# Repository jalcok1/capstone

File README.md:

capstone
========
This repo contains project related documents for the "Marionette DAQ"<br>

- [Visit the Wiki](https://github.com/jalcok1/capstone/wiki)

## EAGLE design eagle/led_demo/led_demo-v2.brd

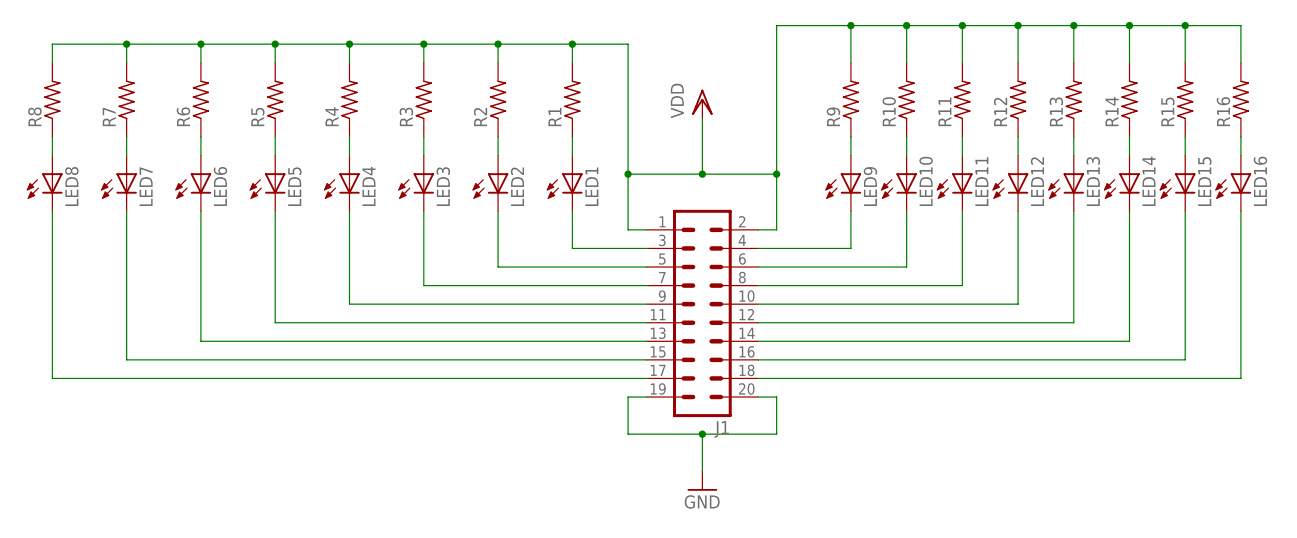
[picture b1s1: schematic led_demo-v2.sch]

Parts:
J1: MA10-2
LED1, LED2, LED3, LED4, LED5, LED6, LED7, LED8, LED9, LED10, LED11, LED12, LED13, LED14, LED15, LED16: LED3MM
R1, R2, R3, R4, R5, R6, R7, R8, R9, R10, R11, R12, R13, R14, R15, R16: R-US_0204/2V; 0204V

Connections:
GND: J1.19, J1.20
unnamed: LED8.A, R8.1
unnamed: LED7.A, R7.1
unnamed: LED6.A, R6.1
unnamed: LED5.A, R5.1
unnamed: LED4.A, R4.1
unnamed: LED3.A, R3.1
unnamed: LED2.A, R2.1
unnamed: LED1.A, R1.1
unnamed: J1.3, LED1.K (C)
unnamed: J1.5, LED2.K (C)
unnamed: J1.7, LED3.K (C)
unnamed: J1.9, LED4.K (C)
unnamed: J1.11, LED5.K (C)
unnamed: J1.13, LED6.K (C)
unnamed: J1.15, LED7.K (C)
unnamed: J1.17, LED8.K (C)
unnamed: J1.4, LED9.K (C)
unnamed: J1.6, LED10.K (C)
unnamed: J1.8, LED11.K (C)
unnamed: J1.10, LED12.K (C)
unnamed: J1.12, LED13.K (C)
unnamed: J1.14, LED14.K (C)
unnamed: J1.16, LED15.K (C)
unnamed: J1.18, LED16.K (C)
unnamed: LED16.A, R16.1
unnamed: LED15.A, R15.1
unnamed: LED14.A, R14.1
unnamed: LED13.A, R13.1
unnamed: LED12.A, R12.1
unnamed: LED11.A, R11.1
unnamed: LED10.A, R10.1
unnamed: LED9.A, R9.1
VDD: J1.1, J1.2, R1.2, R2.2, R3.2, R4.2, R5.2, R6.2, R7.2, R8.2, R9.2, R10.2, R11.2, R12.2, R13.2, R14.2, R15.2, R16.2

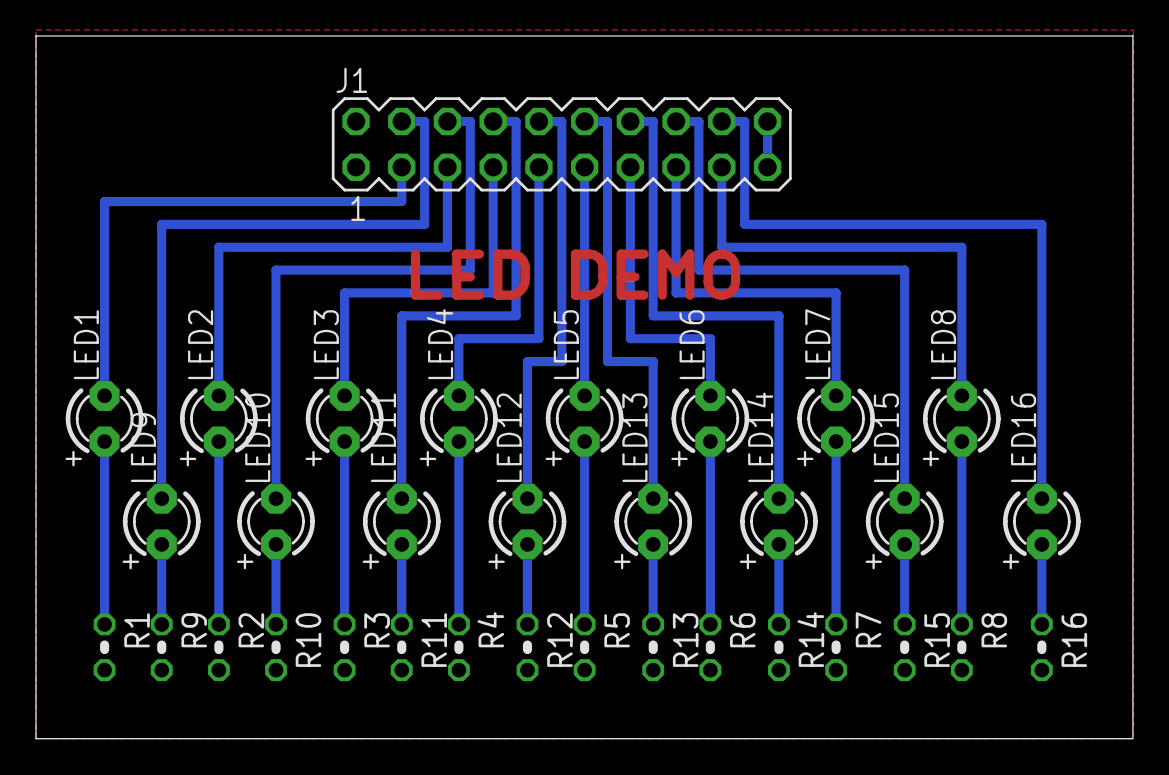
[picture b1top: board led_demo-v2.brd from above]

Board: 2 copper layers, 60.9 x 39.0 mm, 33 parts (0 on the bottom side), 34 nets.

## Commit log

2014-12-17 Daq List
2014-12-17 Empty Commit Message
2014-12-17 Starting research .xls document for seth and I to use :-)
2014-12-17 Update README.md
    Adding DAQ websites
2014-12-17 Opposition DAQs
2014-12-18 Added one research item and aditional formatting changes
2014-12-18 Added updates from capstone research xls to Research.xls
2014-12-18 Added USB-201 and USB-202 entries to the Research.xls spreadsheet
2014-12-29 Message can't be blank
2014-12-29 creating second research document so seth and I can do research using the same formatt without running into merge conflicts
2014-12-29 Adding new counter and counter resolution columns to Research2.xls spreadsheet
2014-12-29 small changes
2015-01-05 Updated Spreadsheet
2015-01-05 Added Digitial I/O column to Research2.xls and input more data
2015-01-06 More small changes
2015-01-07 DAQ's now show whether they have GPIO or not
2015-01-07 Seth Update
2015-01-09 Added matrix of STM32 MCU's, this list will be used for MCU selection in Marionette
2015-01-09 Added project info to README.md
2015-01-10 Added aditional formatting and highlighted some of the most likely candidates for marionette usage
2015-01-10 Level0 Marionette block diagram table
2015-01-11 Adding first draft of marionette level 0 block diagram
2015-01-11 Repo cleanup. Removed redundant research file.
2015-01-12 Finished rough draft of marionette level 0 block diagram
2015-01-12 finished marionette level 1 block diagram rough draft. level 1 table still needs updating
2015-01-13 Added Level 2 block diagram of the power management system
2015-01-13 Level 2 block diagram
    Updated the Level 2 block diagram to be more uniform and added it to the
    Functional Diagram document.
2015-01-13 Minor Editing to level2 block diagram; changed module name and description in the table
2015-01-13 editing changes
2015-01-13 repo clean up
2015-01-13 more repo cleanup
2015-01-13 repo cleanup.
2015-01-13 Update README.md
    Adding link to the capstone Wiki
2015-01-13 Added some changes, to function diagram
2015-01-14 Week 2 meeting notes 1/13/2015
    All corrections and weekly assignments from weekly meetings will be set up as issues.
2015-01-15 Added Level 0 block diagram changes as per request from week2 meeting
2015-01-15 Remved daq_list.rtf, this document contained redundant information that is also in daq_research.xls
2015-01-15 Level 1 and Level 2 block diagram revisions
    Edited both block diagrams as per our previous discussions. Waiting team
    review review before closing out issue
2015-01-15 Added a decision matrix on page2 of STM32matrix.xlsx
2015-01-17 Created folder for data sheets and added the STM3207i data sheet for reference
2015-01-17 Finished level0 and level1 block diagram changes
2015-01-17 Added Reference, programming, and user manuals
2015-01-18 first pass of marionette pin assignment
2015-01-20 2nd draft functional diagram
2015-01-21 Updated Marionette connections spreadsheet
    Added columns for ETH, SDIO, DAC2, and SYS. Added worksheet reserved for
    the 35 pins used for VDD, VREF, etc.
2015-01-21 formatting changes
2015-01-21 Added reserved pins to pin function sheet and made some formatting changes
2015-01-21 Added color formatting, easier to read
2015-01-25 Added 4 different Marionette configurations
2015-01-25 Adding PDS and Timeline
2015-01-26 Fixed ganttchart formatting errors.
2015-01-27 Informal Presentation for Pin Assignments
    Title says it all.
2015-01-27 removed marionette_pin_assignment.xlsx, this spread sheet is out dated and no longer needed
2015-01-27 Added LJU6 daq
2015-01-27 wk04 weekly progress report
2015-01-27 Started a checklist of hardware/components that will need to be selected
2015-01-27 updated information for hardware to be used list
2015-01-28 Added weekly update for week four.
2015-01-28 Added USART column, also added protection to the table preventing accidental changes to the alternate function matrix.
2015-01-29 Added component_selection.csv, digikey query of possible components to be used
2015-01-29 Added LED page to spreadsheet
2015-01-29 list of digikey querys for possible marionette components
2015-01-29 removed "bad" .csv file
2015-01-30 Adding STM32F407.lbr
2015-01-30 Fixed one pin/port error
2015-01-30 Adding data sheet
2015-01-30 Added justification for power jack component
2015-01-31 Added CMR200T 32.768kHz crystal library
2015-01-31 Adding CMR200T datasheet
2015-01-31 Changed pin names from px to x
2015-01-31 Adding LDO datasheet
2015-01-31 Adding LDO library
2015-02-01 Adding ULPI data sheet
2015-02-01 Addeding Updated XCL206B library
2015-02-01 Added SPS data sheet
2015-02-01 fixed pin coordinates in schematic to incremiments .1 in.
2015-02-02 Adding wk05 progress report
2015-02-02 Update wk05.md
    Editing changes
2015-02-04 Create Week5MeetingNotes.MD
    Added notes from week five weekly meeting
2015-02-04 Added Bill of Materials and Schottkey Diode possibilities
2015-02-04 minor changes
2015-02-04 Updated BOM with new components
2015-02-05 Added 2x10 shrouded header connector
2015-02-05 Adding Shrouded pinheader datasheet
2015-02-07 Added Schottky diode to mBom
2015-02-07 Adding Schottky diode datasheet
2015-02-07 Updated STM32F407
2015-02-07 Updated BOM with capacitors info
2015-02-07 Added datasheets for 16MHz and 32.768 kHz crystals
2015-02-07 Modified the supply1 and supply2 symbols
2015-02-07 Added 16MHz Crystal library
2015-02-07 Updated crystal libraries
2015-02-08 Corrected ABS07L library
2015-02-08 Updated Marionette_connections, ABM7 library, component selection spreadsheet, and bill of materials
2015-02-08 Adding weekly progress report for wk06
2015-02-08 Female Pin Headers
    Added libraries for Female Pin Headers
2015-02-08 Minor edits to 50 pin header
2015-02-10 Edited 40 pin female header. Added name value
2015-02-12 32.768kHz LSE clock data sheet
2015-02-12 Added replacement 32.768kHz crystal and 11uF load capacitors to the BOM
2015-02-12 Adding SWD 2x5 pin header datasheet
2015-02-12 Added SWD connector to mBom
2015-02-13 Added STM32F4xx Errata Sheet
2015-02-14 Added reset switch datasheet and bom info
2015-02-14 This time I really added the pushbutton datasheet and bom info
2015-02-16 Crystal did not have enough gm to start oscilation
2015-02-16 Weekly status report
2015-02-16 Added super cap to mBom and its datasheet
2015-02-16 RGB LED datasheet
2015-02-16 Added RGB LED
2015-02-17 Updated BOM with crystal and required load capacitors
2015-02-17 Adding current limiting resistors for RGB LED
2015-02-17 Created 16MHz oscillator
2015-02-17 Added 16Mhz clock to schematic
2015-02-17 Adding super capacitor operating table
2015-02-17 Added Meeting notes from last week
2015-02-17 Created Week 7 weekly meeting
2015-02-17 Added marks on gpios that can be USARTS
2015-02-19 Adding male right angle headers
2015-02-19 Added another angle male header
2015-02-19 Adding 1.8V LDO datasheet
2015-02-19 Added 1.8V LDO to bom
2015-02-19 changed RTC_REFIN to GPIO, we arent using RTC_REFIN
2015-02-19 Added 16MHz crystal to mBom
2015-02-21 Added DAC chip
2015-02-21 Selected USART pins to drive external DAC
2015-02-22 Updated gantt chart to reflect updated timeline and address future events
2015-02-22 Added red LED
2015-02-22 updated bom and apparently gantt chart
2015-02-22 updated bom
2015-02-23 Added 0.05" header
2015-02-23 Edited 0.05" header info
2015-02-23 added 24pin 0.05" male header
2015-02-24 Updated Board lead time to three weeks. Extended board population to one week. Adjusted dependancies accordingly
2015-02-24 Added DAC chip datasheet
2015-02-24 Week eight weekly meeting notes
2015-02-25 Updated BOM with CAN transceiver
2015-03-01 Updated BOM and added data sheets for CAN and DAC ICs
2015-03-02 added 11pF capacitor
2015-03-02 Added 0.1uF capacitor
2015-03-02 added 120 ohm resistor
2015-03-02 Added data sheet for 32.768 kHz crystal
2015-03-03 Added a list of potential TVS diodes
2015-03-03 Edited TVS spreadsheet
2015-03-08 Added data sheets for tvs array and LMV344IDR. Updated mBOM to reflect changes
2015-04-13 Adding dac selection table
2015-04-19 Updating BOM still much to do....
2015-05-03 Added color coded compairison sheet
2015-05-03 Updated BOM to reflect latest changes. To Do: -Find a 4.4pF 0603 cap. Digikey or Mouser doesnt seem to have one Consider changing package to 0402. -Look into changing R12 to 649ohms. I cant seem to f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
2015-05-06 Started capstone presentation poster
2015-05-12 Rough draft of test cases
2015-05-17 Updated poster
2015-05-17 Minor editorial updates
2015-05-17 Minor edits
2015-05-17 Yet another minor edit
2015-05-17 Formated special thanks text box
2015-05-18 Added psas logo
2015-05-18 Minor formatting changes
2015-05-19 added updated campairison chart
2015-05-19 formatting cganges
2015-05-21 Added block diagram and changed some layout
2015-05-24 Added timer spreadsheet for ULPI clock
2015-05-25 Minor formattiong changes
2015-05-27 Editorial updates
2015-05-27 Edited the problem statement
2015-05-27 added photo
2015-05-27 Small change to Results
2015-05-27 Addiong marionette poster pdf
2015-05-28 minor updates
2015-05-30 Updated "chosen config" column on pin connections sheet These values now match marionette-v1 pin functions
2015-06-03 Adding LED demo board and gerbers
2015-06-03 changed trace width and isolate thickness to correct for missing traces on A406
2015-06-03 Updated chosen config pin labels
2015-06-03 Adding LED Demo v2 board
2015-06-03 oops uploaded .gpi and not .gbx
2015-06-10 minor editing
2015-06-10 Edited layout
2015-06-10 deleting unnecessary files
2015-06-10 adding block diagrams
2015-06-15 adding flow chart png files for wiki
